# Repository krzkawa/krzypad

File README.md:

# krzypad
A 9-key macropad that I created for my own use-cases. I wanted some more keys next to my keyboard to do things like push-to-talk and other macros mostly for Fusion360 kicad and some rpg games.

## SCHEMATIC

## PCB

## CASE
| BOTTOM                                                                                                                             | TOP          |
|----------------                                                                                                                    |--------------|
| ||

## ASSembly

## BOM

### JLCPCB

-PCB

### 3D Printed

- Case

### Components

- 1 × Seeed Studio XIAO RP2040
- 9 × 1N4148 Diode
- 1 × EC11 Rotary Encoder
- 1 × 0.91″ I²C OLED Display
- 9 × keycaps
- 4 × M3×16mm screw
- 4 × M3×5mm×4mm heatset insert

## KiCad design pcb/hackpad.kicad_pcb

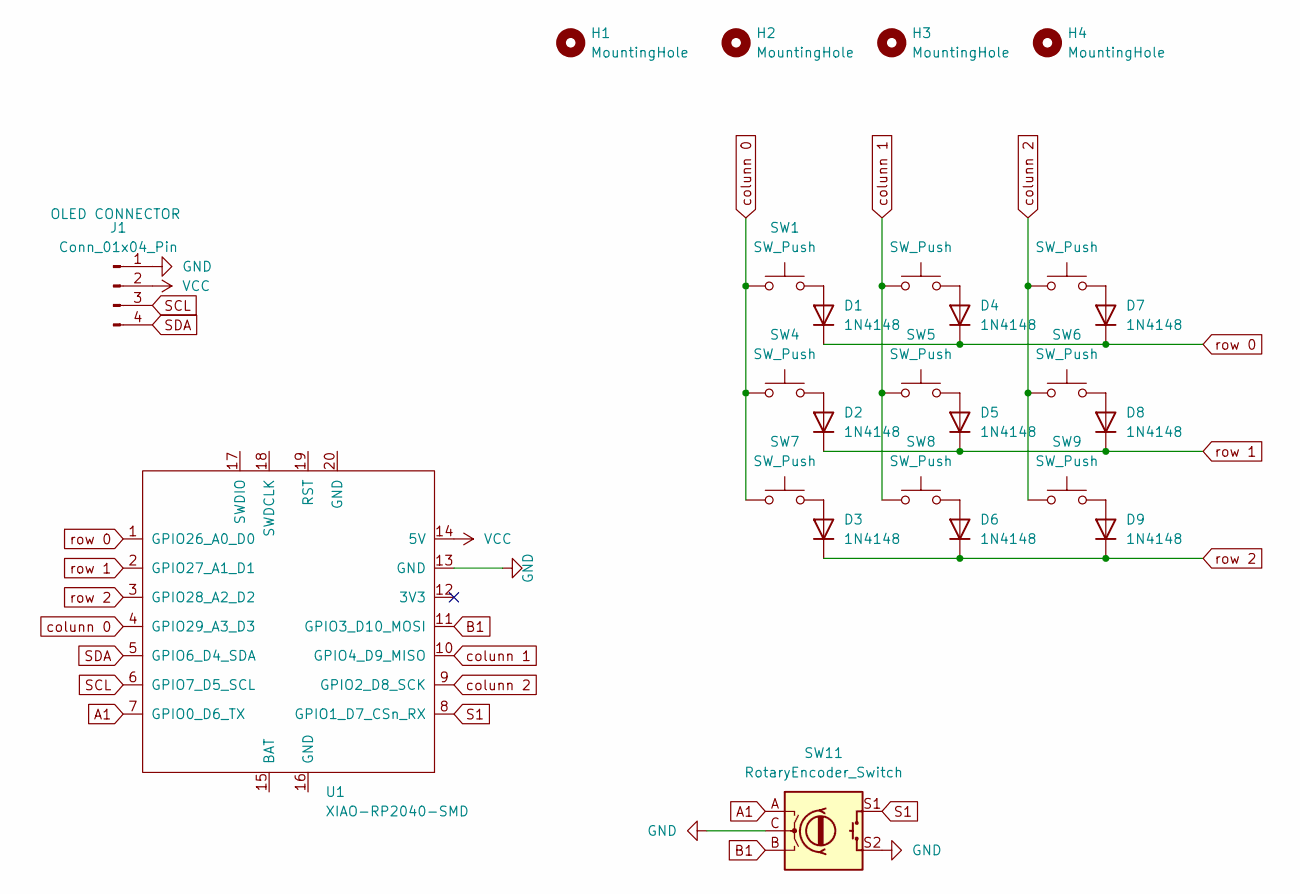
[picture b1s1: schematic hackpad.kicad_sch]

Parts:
D1, D2, D3, D4, D5, D6, D7, D8, D9: 1N4148; D_DO-35_SOD27_P7.62mm_Horizontal
H1, H2, H3, H4: MountingHole; MountingHole_3.2mm_M3_ISO7380
J1: Conn_01x04_Pin; PinHeader_1x04_P2.54mm_Vertical
SW1, SW2, SW3, SW4, SW5, SW6, SW7, SW8, SW9: SW_Push; SW_Cherry_MX_1.00u_PCB
SW11: RotaryEncoder_Switch; RotaryEncoder_Alps_EC11E-Switch_Vertical_H20mm_MountingHoles
U1: XIAO-RP2040-SMD

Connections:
A1: SW11.A, U1.7 (GPIO0_D6_TX)
B1: SW11.B, U1.11 (GPIO3_D10_MOSI)
GND: J1.1, SW11.C, SW11.S2, U1.13 (GND)
unnamed: D1.2 (A), SW1.2
unnamed: D2.2 (A), SW4.2
unnamed: D3.2 (A), SW7.2
unnamed: D4.2 (A), SW2.2
unnamed: D5.2 (A), SW5.2
unnamed: D6.2 (A), SW8.2
unnamed: D7.2 (A), SW3.2
unnamed: D8.2 (A), SW6.2
unnamed: D9.2 (A), SW9.2
S1: SW11.S1, U1.8 (GPIO1_D7_CSn_RX)
SCL: J1.3, U1.6 (GPIO7_D5_SCL)
SDA: J1.4, U1.5 (GPIO6_D4_SDA)
VCC: J1.2, U1.14 (5V)
colunn 0: SW1.1, SW4.1, SW7.1, U1.4 (GPIO29_A3_D3)
colunn 1: SW2.1, SW5.1, SW8.1, U1.10 (GPIO4_D9_MISO)
colunn 2: SW3.1, SW6.1, SW9.1, U1.9 (GPIO2_D8_SCK)
row 0: D1.1 (K), D4.1 (K), D7.1 (K), U1.1 (GPIO26_A0_D0)
row 1: D2.1 (K), D5.1 (K), D8.1 (K), U1.2 (GPIO27_A1_D1)
row 2: D3.1 (K), D6.1 (K), D9.1 (K), U1.3 (GPIO28_A2_D2)

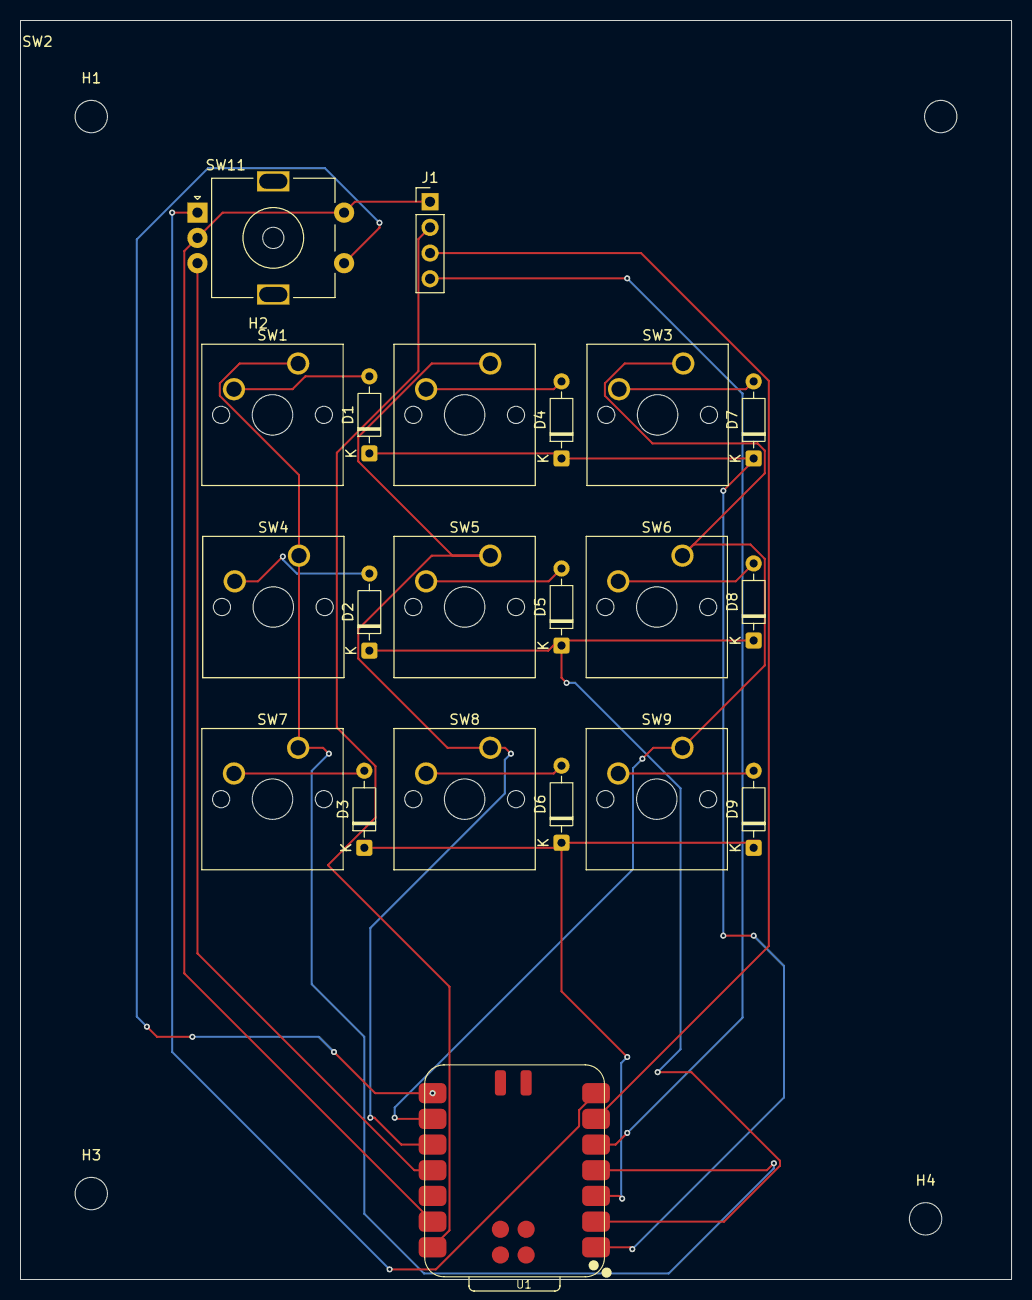
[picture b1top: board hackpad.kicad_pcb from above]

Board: 2 copper layers, 98.0 x 124.5 mm, 25 parts (0 on the bottom side), 22 nets.
